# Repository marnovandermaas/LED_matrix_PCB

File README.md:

# PCB for driving an LED matrix

This PCB is meant to write and read from PMOD pins and drive an LED matrix based on these pins.
There will be a microcontroller that drives the LED matrix so it can also have an independent program to display arbitrary things on the matrix.

The PCB should be able to be powered externally as well as through a battery.
The reason to want to use a battery is that it can then be used as a conference badge to display a name on.

The PCB should connect to the Tiny Tapeout demo board, and specifically with [this factorizer design](https://github.com/marnovandermaas/tiny-factorizer/tree/main) that uses the bidirectional pins solely for output.

## Component Specs

Components should be through hole to ease soldering.

- RP Pico H
    - <https://www.raspberrypi.com/documentation/microcontrollers/raspberry-pi-pico.html>
    - 26 GPIO pins
    - Supply power to VSYS via a Schottky diode
        - ~2.3 V - 5.5 V
- LEDs (KINGBRIGHT TA07-11SEKWA)
    - <https://uk.farnell.com/kingbright/ta07-11sekwa/dot-matrix-0-7-cmn-anode-orange/dp/2080062>
    - Column anode (row cathode)
    - I_F = 10 mA, I_Fmax = 30 mA
    - V_F = 2 V_typ (@ I_F = 10mA)
    - R_7ma = (3.3 V - 2 V) / 7 mA = ~200 Ohm (186 Ohm)

## LED Multiplexing

Row-wise (one row at a time):

- 5 resistors (one per column)
- 5 LEDs max on one pin
    - 10 mA max per LED without transistor
- 7 phase update

Column-wise (one column at a time):

- 7 resistors (one per row)
- 7 LEDs max on one pin
    - 7 mA max per LED without transistor
- 5 phase update

Try using PIO to do the high-frequency stuff?
[PIO emulator](https://github.com/soundpaint/rp2040pio).

## Pins

12 GPIO for the LEDs.

7 GPIO for PMOD output to Tiny Tapeout.

5 GPIO pins for PMOD input from Tiny Tapeout.
Connect some to UART pins.

2 GPIO (or 1 ADC pin) for DIP switches.

Connect RUN pin to a normally-open momentary switch to GND to get a Reset button.

## PCB schematic and design

We'll probably use a cheap PCB manufacturer like: [JLC](https://jlcpcb.com/).
Previously I had also considerd [PCB way](https://www.pcbway.com/).

## Farnell

- 1x [Raspberry Pi Pico H](https://uk.farnell.com/raspberry-pi/raspberry-pi-pico-h/raspberry-pi-board-arm-cortex/dp/3996081)
- 1x [LED Matrix](https://uk.farnell.com/kingbright/ta07-11sekwa/dot-matrix-0-7-cmn-anode-orange/dp/2080062)
- 1x [Reset Switch](https://uk.farnell.com/te-connectivity-alcoswitch/1825910-3/tactile-switch-spst-0-05a-24v/dp/3406898)
- 2x [Schottky Diode](https://uk.farnell.com/stmicroelectronics/bat48/diode-schottky-small-signal/dp/9801472)
- 1x [DIP Switch](https://uk.farnell.com/te-connectivity/ade0204/switch-dil-2way/dp/1123936)
- 1x [Battery Holder](https://uk.farnell.com/keystone/3002/battery-smd-retainer-20mm/dp/1650693)
- 2x [PMOD Header](https://uk.farnell.com/amphenol-fci/10129382-912003blf/btb-conn-header-12pos-2row-2-54mm/dp/3497357)
- 2x [RPi Pico Socket](https://uk.farnell.com/samtec/ces-120-01-t-s/receptacle-2-54mm-single-20way/dp/1667525)
- 5x? [LED Resistors](https://uk.farnell.com/multicomp/mf25-200r/res-200r-1-250mw-axial-metal-film/dp/9341471) although may already have some.
- 4x? [Green LEDs](https://uk.farnell.com/broadcom-limited/hlmp-3950/led-5mm-green/dp/1003226)

## Shift registers

To make sure we can drive all the PMOD input and output, we were thinking it's a good idea to use a shift register to save GPIO pins on the Pico. One thing Elliot mentioned was it would be good to have one full PMOD directly connected to the GPIO so that UART still works.

8-bit parallel input to serial output: [TI SN74HC165N](https://uk.farnell.com/texas-instruments/sn74hc165n/ic-8bit-parallel-load-shift-regist/dp/3120856), 8 inputs with 1 ouput and 2 control signals.

Serial input to 8-bit parallel output: [TI SN74HC595N](https://uk.farnell.com/texas-instruments/sn74hc595n/shift-register-8bit-85deg-c-pdip/dp/3120865), 8 outputs with 1 input and 2 control signals.

Harry's tip: use 74-series logic to get good datasheets.

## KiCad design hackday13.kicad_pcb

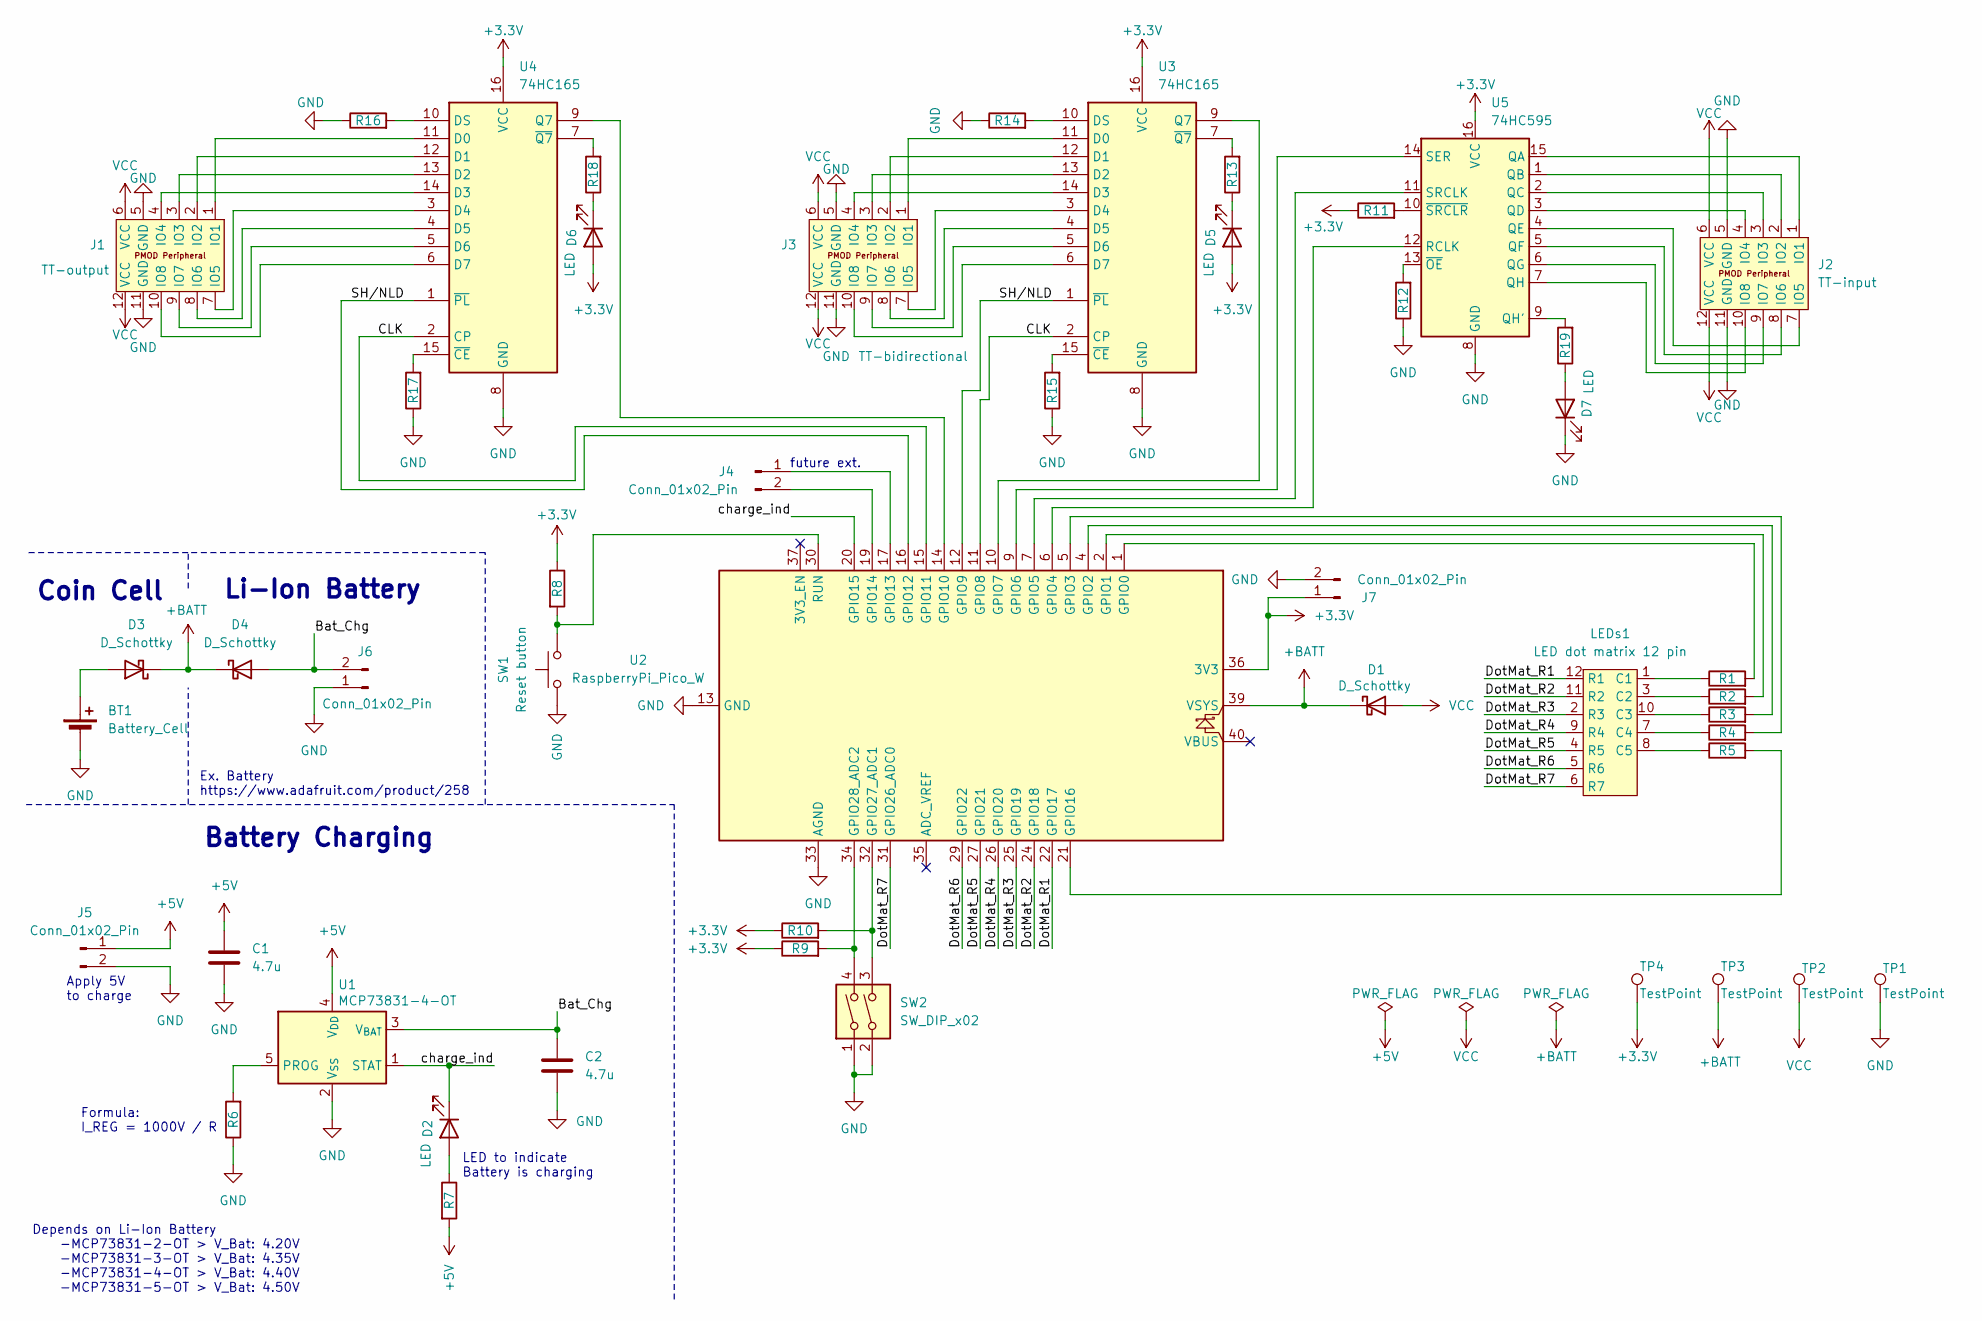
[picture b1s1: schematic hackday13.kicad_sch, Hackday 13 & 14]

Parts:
BT1: Battery_Cell; BatteryHolder_Keystone_3002_1x2032
C1, C2: 4.7u; C_Disc_D7.0mm_W2.5mm_P5.00mm
D1, D3, D4: D_Schottky; D_DO-35_SOD27_P7.62mm_Horizontal
D2, D5, D6, D7: LED; LED_D3.0mm
J1: TT-output; PinHeader_2x06_P2.54mm_PMODPeriph2B
J2: TT-input; PinHeader_2x06_P2.54mm_PMODPeriph2B
J3: TT-bidirectional; PinHeader_2x06_P2.54mm_PMODPeriph2B
J4, J5, J7: Conn_01x02_Pin; PinHeader_1x02_P2.54mm_Vertical
J6: Conn_01x02_Pin; JST_PH_B2B-PH-K_1x02_P2.00mm_Vertical
LEDs1: LED dot matrix 12 pin; LED_dot_matrix_TA07-11SEKWA
R1, R2, R3, R4, R5, R13, R18, R19: 200 Ohm; R_Axial_DIN0207_L6.3mm_D2.5mm_P10.16mm_Horizontal
R6: 2k; R_Axial_DIN0207_L6.3mm_D2.5mm_P10.16mm_Horizontal
R7: 1000 Ohm; R_Axial_DIN0207_L6.3mm_D2.5mm_P10.16mm_Horizontal
R8, R9, R10: 1k; R_Axial_DIN0207_L6.3mm_D2.5mm_P10.16mm_Horizontal
R11, R12, R14, R15, R16, R17: 0; R_Axial_DIN0207_L6.3mm_D2.5mm_P10.16mm_Horizontal
SW1: Reset button; SW_PUSH_6mm
SW2: SW_DIP_x02; SW_DIP_SPSTx02_Slide_9.78x7.26mm_W7.62mm_P2.54mm
TP1, TP2, TP3, TP4: TestPoint; TestPoint_Pad_D3.0mm
U1: MCP73831-4-OT; SOT-23-5
U2: RaspberryPi_Pico_W; RaspberryPi_Pico_Common
U3, U4: 74HC165; DIP-16_W7.62mm
U5: 74HC595; DIP-16_W7.62mm

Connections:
+3.3V: D5.2 (A), D6.2 (A), J7.1, R8.1, R9.1, R10.1, R11.1, TP4.1, U2.36 (3V3), U3.16 (VCC), U4.16 (VCC), U5.16 (VCC)
+5V: C1.1, J5.1, R7.2, U1.4 (V_{DD})
+BATT: D1.1 (K), D3.1 (K), D4.1 (K), TP3.1, U2.39 (VSYS)
/Bat_Chg: C2.1, D4.2 (A), J6.2, U1.3 (V_{BAT})
/CLK: U2.11 (GPIO8), U2.15 (GPIO11), U3.2 (CP), U4.2 (CP)
/DotMat_R1: LEDs1.12 (R1), U2.22 (GPIO17)
/DotMat_R2: LEDs1.11 (R2), U2.24 (GPIO18)
/DotMat_R3: LEDs1.2 (R3), U2.25 (GPIO19)
/DotMat_R4: LEDs1.9 (R4), U2.26 (GPIO20)
/DotMat_R5: LEDs1.4 (R5), U2.27 (GPIO21)
/DotMat_R6: LEDs1.5 (R6), U2.29 (GPIO22)
/DotMat_R7: LEDs1.6 (R7), U2.31 (GPIO26_ADC0)
/SH/NLD: U2.12 (GPIO9), U2.16 (GPIO12), U3.1 (~PL), U4.1 (~PL)
/charge_ind: D2.1 (K), U1.1 (STAT), U2.20 (GPIO15)
GND: BT1.2 (-), C1.2, C2.2, D7.1 (K), J1.5 (GND), J1.11 (GND), J2.5 (GND), J2.11 (GND), J3.5 (GND), J3.11 (GND), J5.2, J6.1, J7.2, R6.1, R12.1, R14.1, R15.1, R16.1, R17.1, SW1.1, SW2.1, SW2.2, TP1.1, U1.2 (V_{SS}), U2.3 (GND), U2.8 (GND), U2.13 (GND), U2.18 (GND), U2.23 (GND), U2.28 (GND), U2.33 (AGND), U2.38 (GND), U3.8 (GND), U4.8 (GND), U5.8 (GND)
unnamed: BT1.1 (+), D3.2 (A)
unnamed: D2.2 (A), R7.1
unnamed: D5.1 (K), R13.1
unnamed: D6.1 (K), R18.1
unnamed: D7.2 (A), R19.1
unnamed: J1.1 (IO1), U4.11 (D0)
unnamed: J1.2 (IO2), U4.12 (D1)
unnamed: J1.3 (IO3), U4.13 (D2)
unnamed: J1.4 (IO4), U4.14 (D3)
unnamed: J1.7 (IO5), U4.3 (D4)
unnamed: J1.8 (IO6), U4.4 (D5)
unnamed: J1.9 (IO7), U4.5 (D6)
unnamed: J1.10 (IO8), U4.6 (D7)
unnamed: J2.1 (IO1), U5.15 (QA)
unnamed: J2.2 (IO2), U5.1 (QB)
unnamed: J2.3 (IO3), U5.2 (QC)
unnamed: J2.4 (IO4), U5.3 (QD)
unnamed: J2.7 (IO5), U5.4 (QE)
unnamed: J2.8 (IO6), U5.5 (QF)
unnamed: J2.9 (IO7), U5.6 (QG)
unnamed: J2.10 (IO8), U5.7 (QH)
unnamed: J3.1 (IO1), U3.11 (D0)
unnamed: J3.2 (IO2), U3.12 (D1)
unnamed: J3.3 (IO3), U3.13 (D2)
unnamed: J3.4 (IO4), U3.14 (D3)
unnamed: J3.7 (IO5), U3.3 (D4)
unnamed: J3.8 (IO6), U3.4 (D5)
unnamed: J3.9 (IO7), U3.5 (D6)
unnamed: J3.10 (IO8), U3.6 (D7)
unnamed: J4.1, U2.17 (GPIO13)
unnamed: J4.2, U2.19 (GPIO14)
unnamed: LEDs1.1 (C1), R1.1
unnamed: LEDs1.3 (C2), R2.1
unnamed: LEDs1.10 (C3), R3.1
unnamed: LEDs1.7 (C4), R4.1
unnamed: LEDs1.8 (C5), R5.1
unnamed: R6.2, U1.5 (PROG)
unnamed: R1.2, U2.1 (GPIO0)
unnamed: R2.2, U2.2 (GPIO1)
unnamed: R3.2, U2.4 (GPIO2)
unnamed: R4.2, U2.5 (GPIO3)
unnamed: U2.6 (GPIO4), U5.12 (RCLK)
unnamed: U2.7 (GPIO5), U5.11 (SRCLK)
unnamed: U2.9 (GPIO6), U5.14 (SER)
unnamed: U2.10 (GPIO7), U3.9 (Q7)
unnamed: U2.14 (GPIO10), U4.9 (Q7)
unnamed: R5.2, U2.21 (GPIO16)
unnamed: R10.2, SW2.3, U2.32 (GPIO27_ADC1)
unnamed: R9.2, SW2.4, U2.34 (GPIO28_ADC2)
unnamed: R8.2, SW1.2, U2.30 (RUN)
unnamed: R14.2, U3.10 (DS)
unnamed: R15.2, U3.15 (~CE)
unnamed: R13.2, U3.7 (~Q7)
unnamed: R16.2, U4.10 (DS)
unnamed: R17.2, U4.15 (~CE)
unnamed: R18.2, U4.7 (~Q7)
unnamed: R19.2, U5.9 (QH')
unnamed: R12.2, U5.13 (~OE)
unnamed: R11.2, U5.10 (~SRCLR)
VCC: D1.2 (A), J1.6 (VCC), J1.12 (VCC), J2.6 (VCC), J2.12 (VCC), J3.6 (VCC), J3.12 (VCC), TP2.1

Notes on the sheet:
Battery Charging
LED to indicate Battery is charging
future ext.
Ex. Battery https://www.adafruit.com/product/258
Coin Cell
Apply 5V to charge
Li-Ion Battery
Depends on Li-Ion Battery -MCP73831-2-OT > V_Bat: 4.20V -MCP73831-3-OT > V_Bat: 4.35V -MCP73831-4-OT > V_Bat: 4.40V -MCP73831-5-OT > V_Bat: 4.50V
Formula: I_REG = 1000V / R

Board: 4 copper layers, 48 parts (0 on the bottom side), 75 nets, no tracks yet.

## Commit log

2024-03-15 Adding tiny tapeout submodule
2024-03-15 First pass at adding PICO and connecting to Pmod
2024-03-15 Add LED dot matrix schematic
2024-03-15 Add footprint for LED dot matrix
2024-03-15 Minor update to schematic
2024-07-12 Add MC14014B shift register
    Also make LED matrix have yellow background
2024-07-12 Connect up shift registers in schematic
2024-07-12 Add schematics for shift regs
    Some other cleanup like wires and component names.
2024-07-12 Label disconnects and power to resolve ERC checks
2024-07-12 Minor layout improvements
2024-07-12 Incomplete attempt at PCB
2024-07-16 Make PCB more compact and remove more ground lines
2026-04-10 [doc] Initial readme
2026-04-10 [proj/schematic] Update Project to KiCad Vers. 9.0.X + add Li-Ion Charger to schematic
2026-04-10 [layout] Start with new 4-L layout
2026-04-10 Through hole shift registers
2026-04-10 Cheaper parallel to serial
2026-04-10 Remove RP2040 as we're not using it
2026-04-10 JLC added as manufacturer
2026-04-10 Component through hole comment
2026-04-10 Tiny factorizer mentioned
2026-04-10 [doc] LEDs added and component list
2026-04-10 [layout] first version of possible layout - review required
2026-04-13 Add initial placement
2026-04-13 Update schematic
2026-04-15 Hackday 19 added to title
